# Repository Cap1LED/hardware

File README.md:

# hardware
PCB layouts and schematics (KiCAD)
This includes power boards and LED boards

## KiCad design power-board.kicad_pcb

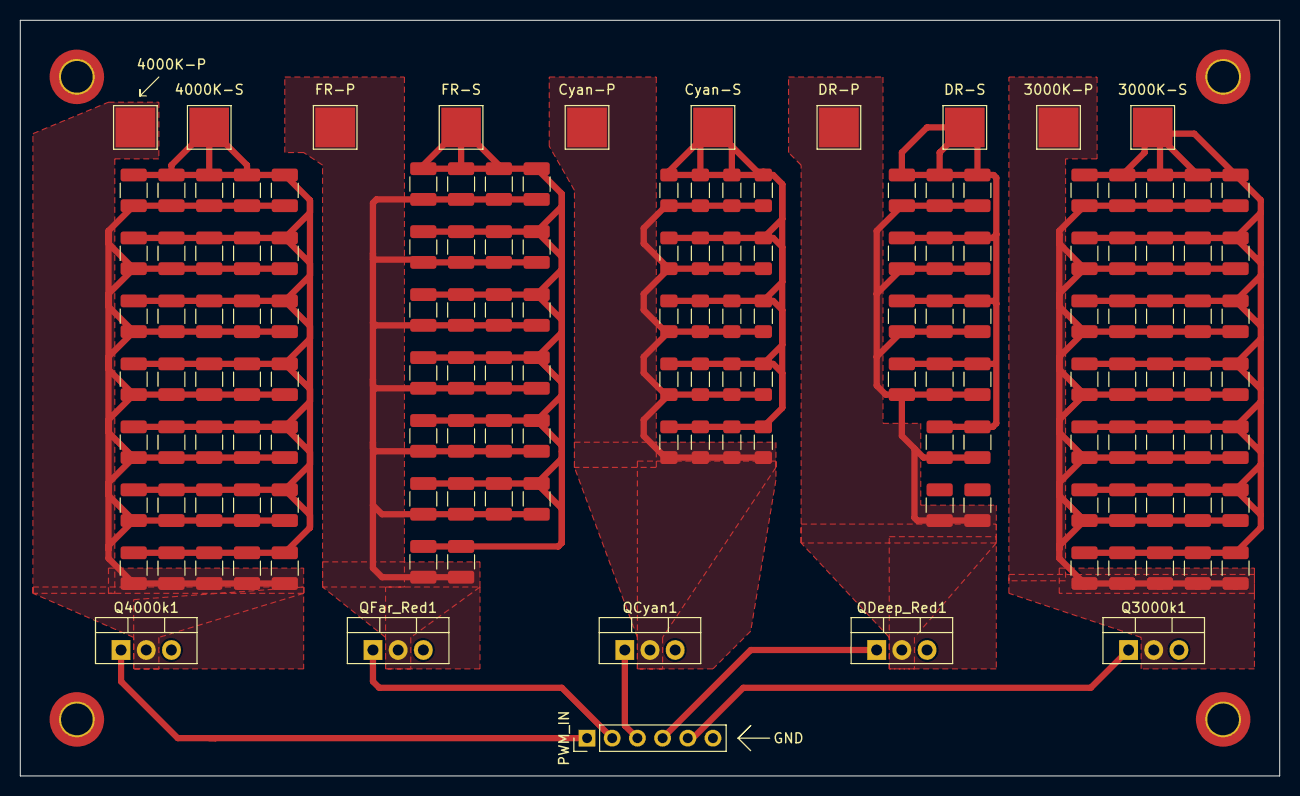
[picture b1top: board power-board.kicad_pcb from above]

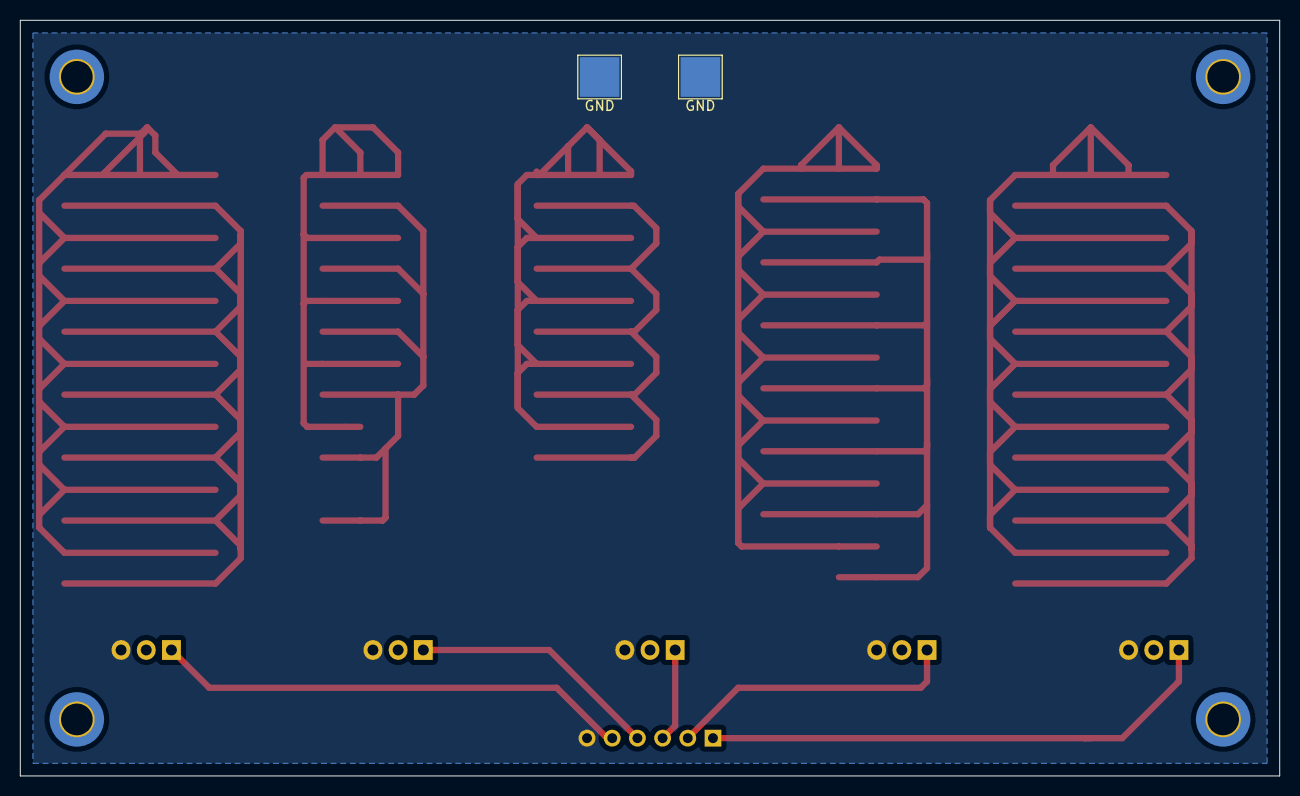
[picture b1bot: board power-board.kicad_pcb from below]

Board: 2 copper layers, 127.0 x 76.2 mm, 18 parts (2 on the bottom side), 11 nets.

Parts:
3000K-P, 3000K-S, 4000K-P, 4000K-S: TestPoint_Pad_4.0x4.0mm
Cyan-P: TestPoint_Pad_4.0x4.0mm
Cyan-S: TestPoint_Pad_4.0x4.0mm
DR-P: TestPoint_Pad_4.0x4.0mm
DR-S: TestPoint_Pad_4.0x4.0mm
FR-P: TestPoint_Pad_4.0x4.0mm
FR-S: TestPoint_Pad_4.0x4.0mm
GND: TestPoint_Pad_4.0x4.0mm
GND#2: TestPoint_Pad_4.0x4.0mm
PWM_IN: PinHeader_1x06_P2.54mm_Vertical
Q3000k1, Q4000k1: IRLZ44N; TO-220-3_Vertical
QCyan1: IRLZ44N; TO-220-3_Vertical
QDeep_Red1: IRLZ44N; TO-220-3_Vertical
QFar_Red1: IRLZ44N; TO-220-3_Vertical

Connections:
GND: GND.1, GND#2.1, PWM_IN.6, Q3000k1.3, Q4000k1.3, QCyan1.3, QDeep_Red1.3, QFar_Red1.3
unnamed: PWM_IN.2, QFar_Red1.1
unnamed: FR-P.1, QFar_Red1.2
unnamed: PWM_IN.1, Q4000k1.1
unnamed: PWM_IN.3, QCyan1.1
unnamed: PWM_IN.4, QDeep_Red1.1
unnamed: PWM_IN.5, Q3000k1.1
unnamed: 3000K-P.1, Q3000k1.2
unnamed: 4000K-P.1, Q4000k1.2
unnamed: DR-P.1, QDeep_Red1.2
unnamed: Cyan-P.1, QCyan1.2

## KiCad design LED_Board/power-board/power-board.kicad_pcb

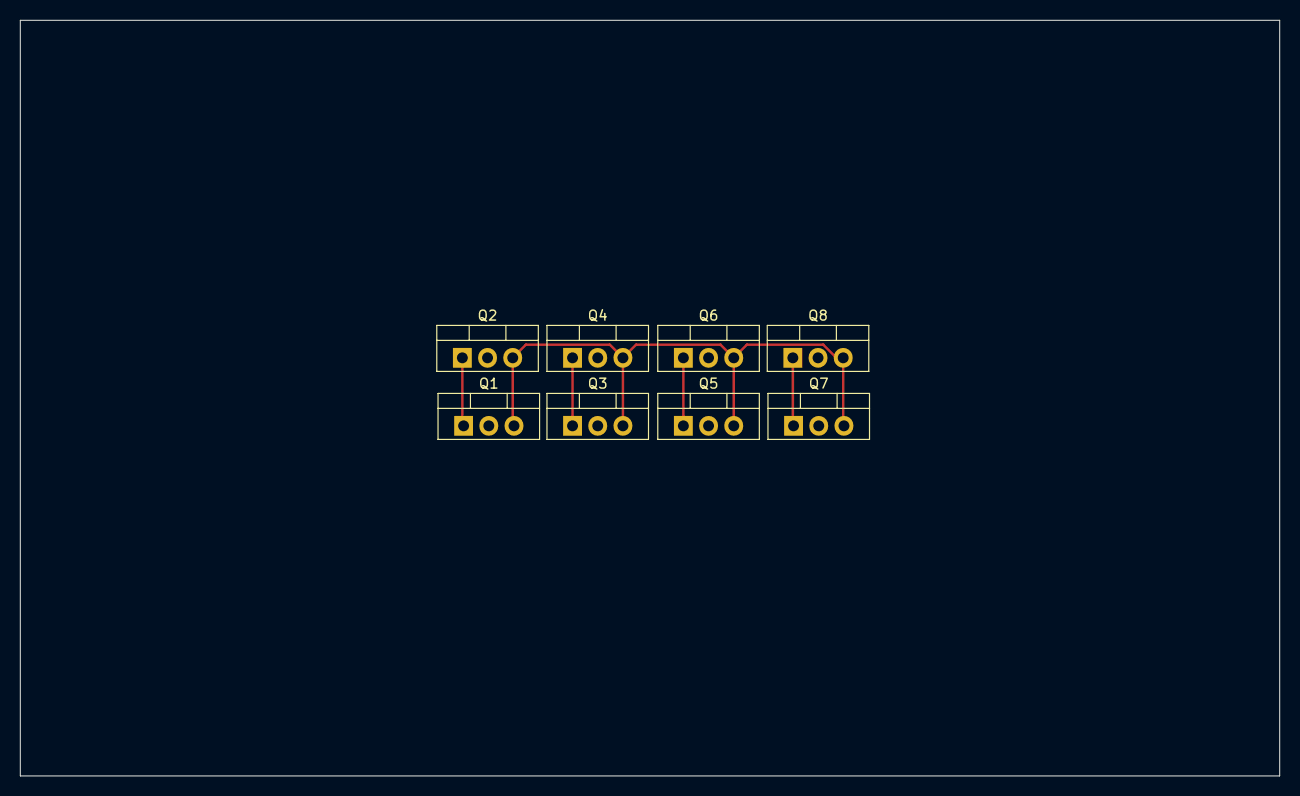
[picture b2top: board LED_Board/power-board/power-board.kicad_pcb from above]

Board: 2 copper layers, 127.0 x 76.2 mm, 8 parts (0 on the bottom side), 5 nets.

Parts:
Q1, Q2, Q3, Q4, Q5, Q6, Q7, Q8: IRLZ44N; TO-220-3_Vertical

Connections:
GND: Q1.3, Q2.3, Q3.3, Q4.3, Q5.3, Q6.3, Q7.3, Q8.3
unnamed: Q1.1, Q2.1
unnamed: Q3.1, Q4.1
unnamed: Q5.1, Q6.1
unnamed: Q7.1, Q8.1

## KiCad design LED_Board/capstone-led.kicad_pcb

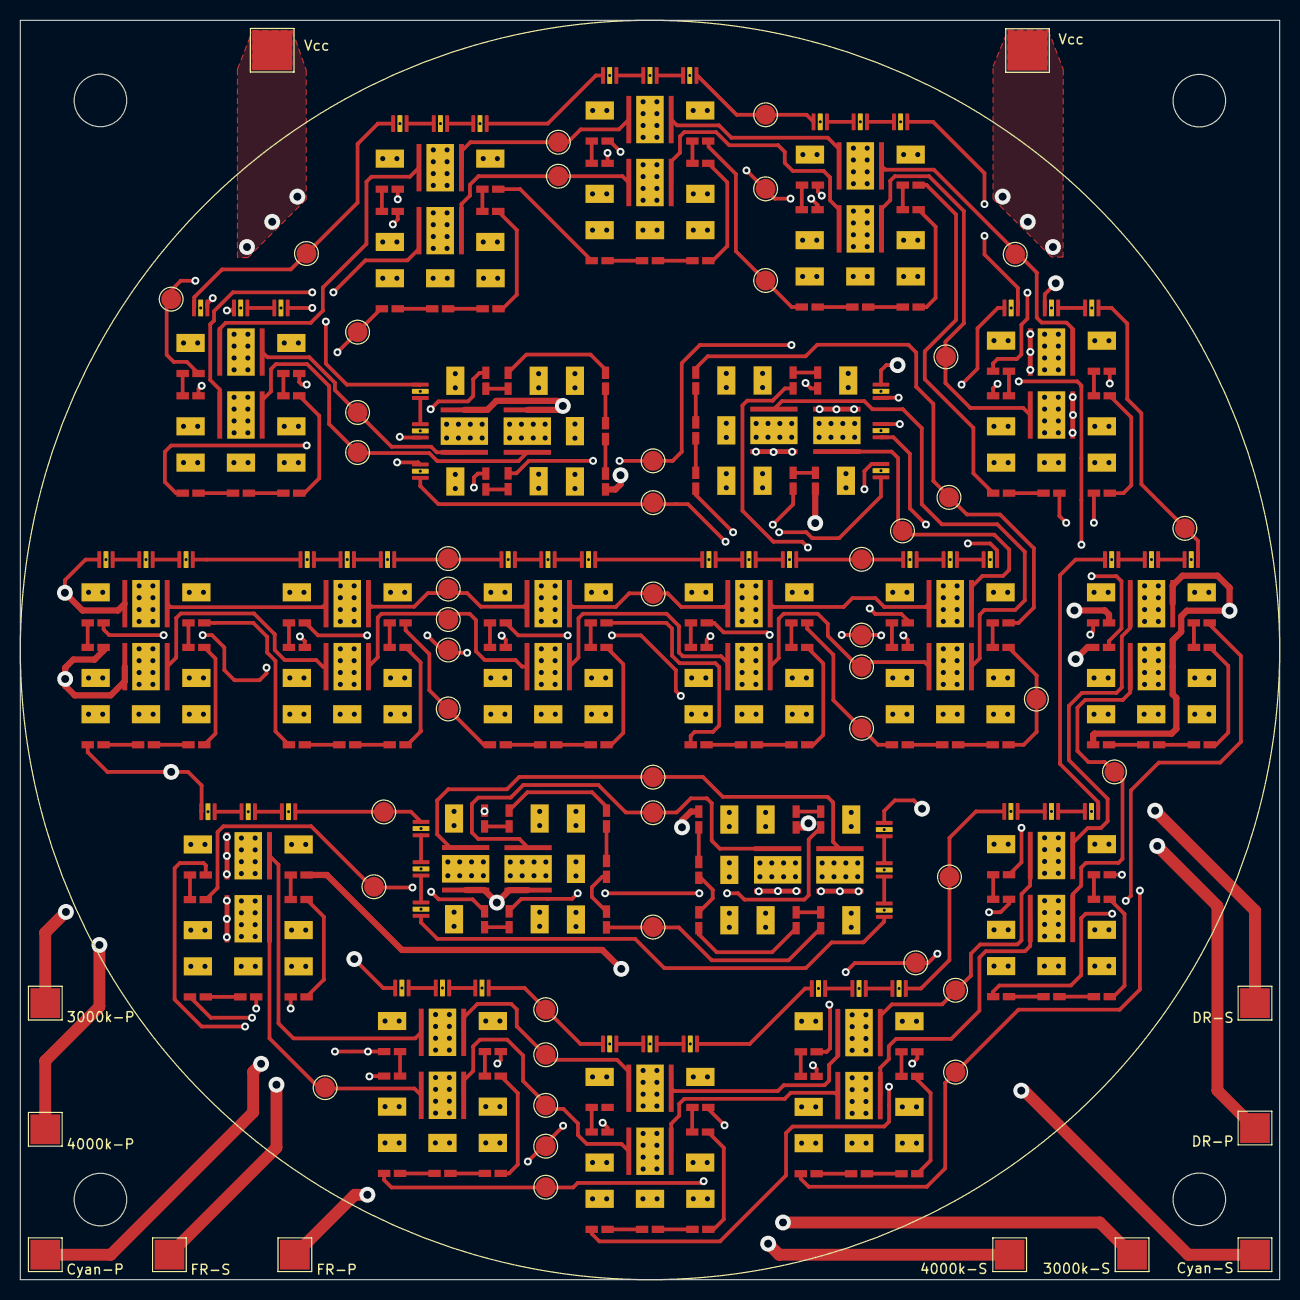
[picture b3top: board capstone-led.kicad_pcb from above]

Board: 4 copper layers, 127.0 x 127.0 mm, 230 parts (0 on the bottom side), 209 nets.

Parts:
3P1: TestPoint_Pad_D2.0mm
3000k-P, 3000k-S, 4000k-P, 4000k-S: TestPoint_Pad_3.0x3.0mm
CP1: TestPoint_Pad_D2.0mm
Cyan-P: TestPoint_Pad_3.0x3.0mm
Cyan-S: TestPoint_Pad_3.0x3.0mm
D1, D2, D3, D5, D11, D13, D14, D15, D25, D26, D27, D37, D38, D39, D49, D50, D51, D61, D62, D63: MHBBWT-0000000C0HD430H; 4000k
D4, D7, D8, D9, D10, D19, D20, D21, D31, D32, D33, D43, D44, D45, D55, D56, D57, D67, D68, D69: MHBBWT-0000000C0HE240H; 4000k
D18, D81, D82, D83, D84, D85, D94, D95, D96, D97, D98, D107, D108, D109, D110, D111, D120, D121, D122, D123, D124, D133, D134, D135, D136, D137, D141, D142, D143, D144, D145, D146, D147, D148, D149, D150, D154, D155, D156, D157, D158, D162, D163, D164, D165, D166, D170, D171, D172, D173, D174, D178, D179, D181, D182, D186, D187, D188, D189, D190, D194, D195, D196, D197, D198, D202, D203, D204, D205, D206, D210, D211, D212, D213, D214, D218, D219, D220, D221, D222, D226, D227, D228, D229, D230, D234, D235, D236, D237, D238: LXML-PF01; Reds
D34, D36, D41, D46, D48, D53, D58, D60, D65, D73, D74, D75, D86, D87, D88, D99, D100, D101, D112, D113, D114, D125, D126, D127, D138, D139, D140, D151, D152, D153, D159, D160, D161, D167, D168, D169, D175, D176, D177, D183, D184, D185, D191, D192, D193, D199, D200, D201, D207, D208, D209, D215, D216, D217, D223, D224, D225, D231, D232, D233: L1CU-CYN1; Cyan
D76, D77, D78, D79, D80, D89, D90, D91, D92, D93, D102, D103, D104, D105, D106, D115, D116, D117, D118, D119, D128, D129, D130, D131, D132: LXM3-PD01; Reds
DR-P: TestPoint_Pad_3.0x3.0mm
DR-S: TestPoint_Pad_3.0x3.0mm
FR-P: TestPoint_Pad_3.0x3.0mm
FR-S: TestPoint_Pad_3.0x3.0mm
FRP1: TestPoint_Pad_D2.0mm
Vcc: TestPoint_Pad_4.0x4.0mm
Vcc#2: TestPoint_Pad_4.0x4.0mm

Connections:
unnamed: D1.2, D13.1
unnamed: D1.3, D2.3, D3.3, D4.3, D5.3, D7.3, D8.3, D9.3, D10.3, D11.3, D13.3, D14.3, D15.3, D18.3, D19.3, D20.3, D21.3, D25.3, D26.3, D27.3, D31.3, D32.3, D33.3, D34.3, D36.3, D37.3, D38.3, D39.3, D41.3, D43.3, D44.3, D45.3, D46.3, D48.3, D49.3, D50.3, D51.3, D53.3, D55.3, D56.3, D57.3, D58.3, D60.3, D61.3, D62.3, D63.3, D65.3, D67.3, D68.3, D69.3, D73.3, D74.3, D75.3, D76.3, D77.3, D78.3, D79.3, D80.3, D81.3, D82.3, D83.3, D84.3, D85.3, D86.3, D87.3, D88.3, D89.3, D90.3, D91.3, D92.3, D93.3, D94.3, D95.3, D96.3, D97.3, D98.3, D99.3, D100.3, D101.3, D102.3, D103.3, D104.3, D105.3, D106.3, D107.3, D108.3, D109.3, D110.3, D111.3, D112.3, D113.3, D114.3, D115.3, D116.3, D117.3, D118.3, D119.3, D120.3, D121.3, D122.3, D123.3, D124.3, D125.3, D126.3, D127.3, D128.3, D129.3, D130.3, D131.3, D132.3, D133.3, D134.3, D135.3, D136.3, D137.3, D138.3, D139.3, D140.3, D141.3, D142.3, D143.3, D144.3, D145.3, D146.3, D147.3, D148.3, D149.3, D150.3, D151.3, D152.3, D153.3, D154.3, D155.3, D156.3, D157.3, D158.3, D159.3, D160.3, D161.3, D162.3, D163.3, D164.3, D165.3, D166.3, D167.3, D168.3, D169.3, D170.3, D171.3, D172.3, D173.3, D174.3, D175.3, D176.3, D177.3, D178.3, D179.3, D181.3, D182.3, D183.3, D184.3, D185.3, D186.3, D187.3, D188.3, D189.3, D190.3, D191.3, D192.3, D193.3, D194.3, D195.3, D196.3, D197.3, D198.3, D199.3, D200.3, D201.3, D202.3, D203.3, D204.3, D205.3, D206.3, D207.3, D208.3, D209.3, D210.3, D211.3, D212.3, D213.3, D214.3, D215.3, D216.3, D217.3, D218.3, D219.3, D220.3, D221.3, D222.3, D223.3, D224.3, D225.3, D226.3, D227.3, D228.3, D229.3, D230.3, D231.3, D232.3, D233.3, D234.3, D235.3, D236.3, D237.3, D238.3
unnamed: D4.2, D10.1
unnamed: 3000k-S.1, D10.2
unnamed: D5.2, D11.1
unnamed: 4000k-S.1, D11.2
unnamed: D13.2, D25.1
unnamed: D2.2, D14.1
unnamed: D14.2, D26.1
unnamed: D3.2, D15.1
unnamed: D15.2, D27.1
unnamed: D18.2, D188.1
unnamed: D7.2, D19.1
unnamed: D19.2, D31.1
unnamed: D8.2, D20.1
unnamed: D20.2, D32.1
unnamed: D9.2, D21.1
unnamed: D21.2, D33.1
unnamed: D25.2, D37.1
unnamed: D26.2, D38.1
unnamed: D27.2, D39.1
unnamed: D31.2, D43.1
unnamed: D32.2, D44.1
unnamed: D33.2, D45.1
unnamed: D34.2, D36.1
unnamed: D36.2, D41.1
unnamed: D37.2, D49.1
unnamed: D38.2, D50.1
unnamed: D39.2, D51.1
unnamed: D41.2, D46.1
unnamed: D43.2, D55.1
unnamed: D44.2, D56.1
unnamed: D45.2, D57.1
unnamed: D46.2, D48.1
unnamed: D48.2, D53.1
unnamed: D49.2, D61.1
unnamed: D50.2, D62.1
unnamed: D51.2, D63.1
unnamed: D53.2, D58.1
unnamed: D55.2, D67.1
unnamed: D56.2, D68.1
unnamed: D57.2, D69.1
unnamed: D58.2, D60.1
unnamed: D60.2, D65.1
unnamed: 3000k-P.1, D61.2, D62.2, D63.2
unnamed: Cyan-S.1, D65.2
unnamed: 4000k-P.1, D67.2, D68.2, D69.2
unnamed: D73.2, D86.1
unnamed: D74.2, D87.1
unnamed: D75.2, D88.1
unnamed: D76.2, D89.1
unnamed: D77.2, D90.1
unnamed: D78.2, D91.1
unnamed: D79.2, D92.1
unnamed: D80.2, D93.1
unnamed: D81.2, D94.1
unnamed: D82.2, D95.1
unnamed: D83.2, D96.1
unnamed: D84.2, D97.1
unnamed: D85.2, D98.1
unnamed: D86.2, D99.1
unnamed: D87.2, D100.1
unnamed: D100.2, D113.1
unnamed: D88.2, D101.1
unnamed: D101.2, D114.1
unnamed: D89.2, D102.1
unnamed: D102.2, D115.1
unnamed: D90.2, D103.1
unnamed: D103.2, D116.1
unnamed: D91.2, D104.1
unnamed: D104.2, D117.1
unnamed: D92.2, D105.1
unnamed: D105.2, D118.1
unnamed: D93.2, D106.1
unnamed: D106.2, D119.1
unnamed: D94.2, D107.1
unnamed: D107.2, D120.1
unnamed: D95.2, D108.1
unnamed: D108.2, D121.1
unnamed: D96.2, D109.1
unnamed: D109.2, D122.1
unnamed: D97.2, D110.1
unnamed: D110.2, D123.1
unnamed: D98.2, D111.1
unnamed: D111.2, D124.1
unnamed: D99.2, D112.1
unnamed: D112.2, D125.1
unnamed: D113.2, D126.1
unnamed: D114.2, D127.1
unnamed: D115.2, D128.1
unnamed: D116.2, D129.1
unnamed: D117.2, D130.1
unnamed: D118.2, D131.1
unnamed: D119.2, D132.1
unnamed: D120.2, D133.1
unnamed: D121.2, D134.1
unnamed: D122.2, D135.1
unnamed: D123.2, D136.1
unnamed: D124.2, D137.1
unnamed: D125.2, D138.1
unnamed: D126.2, D139.1
unnamed: D127.2, D140.1
unnamed: D77.1, D128.2
unnamed: D78.1, D129.2
unnamed: D79.1, D130.2
unnamed: D80.1, D131.2
unnamed: D132.2, DR-S.1
unnamed: D133.2, D141.1
unnamed: D134.2, D142.1
unnamed: D135.2, D143.1
unnamed: D136.2, D144.1
unnamed: D137.2, D145.1
unnamed: D138.2, D151.1
unnamed: D139.2, D152.1
unnamed: D140.2, D153.1
unnamed: D82.1, D141.2
unnamed: D83.1, D142.2
unnamed: D84.1, D143.2
unnamed: D85.1, D144.2
unnamed: D145.2, D190.2, D238.2, FR-P.1
unnamed: D146.2, D154.1
unnamed: D147.1, D186.2
unnamed: D147.2, D155.1
unnamed: D148.1, D187.2
unnamed: D148.2, D156.1
unnamed: D149.1, D188.2
unnamed: D149.2, D157.1
unnamed: D150.1, D189.2
unnamed: D150.2, D158.1
unnamed: D151.2, D159.1
unnamed: D152.2, D160.1
unnamed: D153.2, D161.1
unnamed: D154.2, D162.1
unnamed: D155.2, D163.1
unnamed: D156.2, D164.1
unnamed: D157.2, D165.1
unnamed: D158.2, D166.1
unnamed: D159.2, D167.1
unnamed: D160.2, D168.1
unnamed: D161.2, D169.1
unnamed: D162.2, D170.1
unnamed: D163.2, D171.1
unnamed: D164.2, D172.1
unnamed: D165.2, D173.1
unnamed: D166.2, D174.1
unnamed: D167.2, D175.1
unnamed: D168.2, D176.1
unnamed: D169.2, D177.1
unnamed: D170.2, D178.1
unnamed: D171.2, D179.1
unnamed: D18.1, D172.2
unnamed: D173.2, D181.1
unnamed: D174.2, D182.1
unnamed: D175.2, D183.1
unnamed: D176.2, D184.1
unnamed: D177.2, D185.1
unnamed: D178.2, D186.1
unnamed: D179.2, D187.1
unnamed: D181.2, D189.1
unnamed: D182.2, D190.1
unnamed: D183.2, D191.1
unnamed: D184.2, D192.1
unnamed: D185.2, D193.1
unnamed: D191.2, D199.1
unnamed: D192.2, D200.1
unnamed: D193.2, D201.1
unnamed: D194.2, D202.1
unnamed: D195.1, D234.2
unnamed: D195.2, D203.1
unnamed: D196.1, D235.2
unnamed: D196.2, D204.1
unnamed: D197.1, D236.2
unnamed: D197.2, D205.1
unnamed: D198.1, D237.2
unnamed: D198.2, D206.1
unnamed: D199.2, D207.1
unnamed: D200.2, D208.1
unnamed: D201.2, D209.1
unnamed: D202.2, D210.1
unnamed: D203.2, D211.1
unnamed: D204.2, D212.1
unnamed: D205.2, D213.1
unnamed: D206.2, D214.1
unnamed: D207.2, D215.1
unnamed: D208.2, D216.1
unnamed: D209.2, D217.1
unnamed: D210.2, D218.1
unnamed: D211.2, D219.1
unnamed: D212.2, D220.1
unnamed: D213.2, D221.1
unnamed: D214.2, D222.1
unnamed: D215.2, D223.1
unnamed: D216.2, D224.1
unnamed: D217.2, D225.1
unnamed: D218.2, D226.1
unnamed: D219.2, D227.1
unnamed: D220.2, D228.1
unnamed: D221.2, D229.1
unnamed: D222.2, D230.1
unnamed: D223.2, D231.1
unnamed: D224.2, D232.1
unnamed: D225.2, D233.1
unnamed: D226.2, D234.1
unnamed: D227.2, D235.1
unnamed: D228.2, D236.1
unnamed: D229.2, D237.1
unnamed: D230.2, D238.1
unnamed: Cyan-P.1, D231.2, D232.2, D233.2
VCC: D1.1, D2.1, D3.1, D4.1, D5.1, D7.1, D8.1, D9.1, D34.1, D73.1, D74.1, D75.1, D76.1, D81.1, D146.1, D194.1, Vcc.1, Vcc#2.1

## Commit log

2020-09-25 Test
2021-04-15 LED Board added
    Pending minor changes: screw holes, filled zones for Vcc connections
2021-04-15 Initial hardware commit
    Semi-final revision of the power board. Still missing ground
2021-04-15 Drill Holes, Vcc Fill Zones, Thicker Vcc Traces
    Finalizing design for review before sending to manufacturing
2021-04-20 Add Ground pads on back
    The last step before gerber and drill
2021-04-20 Fix pad netlist and refill copper zone
2021-04-20 Minor fixes before Gerber Generation
2021-04-27 Final fixes for JLCPCB
    Oval holes changed to circular in LED thermal pad
